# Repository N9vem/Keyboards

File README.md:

# Keyboards
My public keyboards, layouts or keyboard ideas, mostly work in progress.

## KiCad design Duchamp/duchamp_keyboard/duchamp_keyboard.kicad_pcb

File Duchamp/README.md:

Duchamp keyboard - The first pcb I ever finished

WARNING this pcb is untested yet

The board uses the larger pro micro which is mounted normally (the USB is facing downwards).

This PCB is may not be compatible with planck cases: the switch distance is 19.05 mm.

PCB size: 76 x 223.5 mm

BOM
- 1 large pro micro
- 47 Cherry MX style switch (clear body)
- 47 high speed diode, MiniMELF or through-hole
- 47 WS2812B LED
- 47 1206 capacitor ~100 nF
- 1 1206 resistor 300-500 Ω

Optional
- 1 EVQP0 switch for reset button

KNOWN ISSUES
- the switch distance are set for standard instead of 19 mm which can make them incompatible with planck switch plates.
- no mounting holes

The case for the keyboard is untested

<br />This work is licensed under a <a rel="license" href="http://creativecommons.org/licenses/by-sa/4.0/">Creative Commons Attribution-ShareAlike 4.0 International License</a>.

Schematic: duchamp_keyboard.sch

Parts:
C101, C102, C103, C104, C105, C106, C107, C108, C109, C110, C111, C112, C113, C114, C115, C116, C117, C118, C119, C120, C121, C122, C123, C124, C125, C126, C127, C128, C129, C130, C131, C132, C133, C134, C135, C136, C137, C138, C139, C140, C141, C142, C143, C144, C145, C146, C147: C_Small; C_1206_HandSoldering
D101, D102, D103, D104, D105, D106, D107, D108, D109, D110, D111, D112, D113, D114, D115, D116, D117, D118, D119, D120, D121, D122, D123, D124, D125, D126, D127, D128, D129, D130, D131, D132, D133, D134, D135, D136, D137, D138, D139, D140, D141, D142, D143, D144, D145, D146, D147: D; D_MiniMELF_Universal_Back
J_burn1: Conn_01x05; Pin_Header_Angled_1x05_Pitch2.00mm
J_ledstrip1: Conn_01x03; Pin_Header_Straight_1x03_Pitch2.00mm
LED101, LED102, LED103, LED104, LED105, LED106, LED107, LED108, LED109, LED110, LED111, LED112, LED113, LED114, LED115, LED116, LED117, LED118, LED119, LED120, LED121, LED122, LED123, LED124, LED125, LED126, LED127, LED128, LED129, LED130, LED131, LED132, LED133, LED134, LED135, LED136, LED137, LED138, LED139, LED140, LED141, LED142, LED143, LED144, LED145, LED146, LED147: WS2812B; CHERRY_MX_LED_WS2812b
R_DIN1: R; R_1206_HandSoldering
SW101: s1; CHERRY_PCB_100H
SW102: s2; CHERRY_PCB_100H
SW103: s3; CHERRY_PCB_100H
SW104: s4; CHERRY_PCB_100H
SW105: s5; CHERRY_PCB_100H
SW106: s6; CHERRY_PCB_100H
SW107: s7; CHERRY_PCB_100H
SW108: s8; CHERRY_PCB_100H
SW109: s9; CHERRY_PCB_100H
SW110: s10; CHERRY_PCB_100H
SW111: s11; CHERRY_PCB_100H
SW112: s12; CHERRY_PCB_100H
SW113: s13; CHERRY_PCB_100H
SW114: s14; CHERRY_PCB_100H
SW115: s15; CHERRY_PCB_100H
SW116: s16; CHERRY_PCB_100H
SW117: s17; CHERRY_PCB_100H
SW118: s18; CHERRY_PCB_100H
SW119: s19; CHERRY_PCB_100H
SW120: s20; CHERRY_PCB_100H
SW121: s21; CHERRY_PCB_100H
SW122: s22; CHERRY_PCB_100H
SW123: s23; CHERRY_PCB_100H
SW124: s24; CHERRY_PCB_100H
SW125: s25; CHERRY_PCB_100H
SW126: s26; CHERRY_PCB_100H
SW127: s27; CHERRY_PCB_100H
SW128: s28; CHERRY_PCB_100H
SW129: s29; CHERRY_PCB_100H
SW130: s30; CHERRY_PCB_100H
SW131: s31; CHERRY_PCB_100H
SW132: s32; CHERRY_PCB_100H
SW133: s33; CHERRY_PCB_100H
SW134: s34; CHERRY_PCB_100H
SW135: s35; CHERRY_PCB_100H
SW136: s36; CHERRY_PCB_100H
SW137: s37; CHERRY_PCB_100H
SW138: s38; CHERRY_PCB_100H
SW139: s39; CHERRY_PCB_100H
SW140: s40; CHERRY_PCB_100H
SW141: s41; CHERRY_PCB_100H
SW142: s42; CHERRY_PCB_200H
SW143: s43; CHERRY_PCB_100H
SW144: s44; CHERRY_PCB_100H
SW145: s45; CHERRY_PCB_100H
SW146: s46; CHERRY_PCB_100H
SW147: s47; CHERRY_PCB_100H
U101: ProMicro_large
res1: SW_Push; SW_SPST_EVQP0

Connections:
COL0: D101.1 (K), D113.1 (K), D125.1 (K), D137.1 (K), U101.1
COL1: D102.1 (K), D114.1 (K), D126.1 (K), D138.1 (K), U101.2
COL2: D103.1 (K), D115.1 (K), D127.1 (K), D139.1 (K), U101.10
COL3: D104.1 (K), D116.1 (K), D128.1 (K), D140.1 (K), U101.11
COL4: D105.1 (K), D117.1 (K), D129.1 (K), D141.1 (K), U101.13
COL5: D106.1 (K), D118.1 (K), D130.1 (K), D142.1 (K), U101.14
COL6: D107.1 (K), D119.1 (K), D131.1 (K), U101.15
COL7: D108.1 (K), D120.1 (K), D132.1 (K), D143.1 (K), U101.16
COL8: D109.1 (K), D121.1 (K), D133.1 (K), D144.1 (K), U101.17
COL9: D110.1 (K), D122.1 (K), D134.1 (K), D145.1 (K), U101.18
COL10: D111.1 (K), D123.1 (K), D135.1 (K), D146.1 (K), U101.19
COL11: D112.1 (K), D124.1 (K), D136.1 (K), D147.1 (K), U101.20
DIN: R_DIN1.1, U101.12
GND: C101.1, C102.1, C103.1, C104.1, C105.1, C106.1, C107.1, C108.1, C109.1, C110.1, C111.1, C112.1, C113.1, C114.1, C115.1, C116.1, C117.1, C118.1, C119.1, C120.1, C121.1, C122.1, C123.1, C124.1, C125.1, C126.1, C127.1, C128.1, C129.1, C130.1, C131.1, C132.1, C133.1, C134.1, C135.1, C136.1, C137.1, C138.1, C139.1, C140.1, C141.1, C142.1, C143.1, C144.1, C145.1, C146.1, C147.1, J_ledstrip1.1, LED101.3 (VSS), LED102.3 (VSS), LED103.3 (VSS), LED104.3 (VSS), LED105.3 (VSS), LED106.3 (VSS), LED107.3 (VSS), LED108.3 (VSS), LED109.3 (VSS), LED110.3 (VSS), LED111.3 (VSS), LED112.3 (VSS), LED113.3 (VSS), LED114.3 (VSS), LED115.3 (VSS), LED116.3 (VSS), LED117.3 (VSS), LED118.3 (VSS), LED119.3 (VSS), LED120.3 (VSS), LED121.3 (VSS), LED122.3 (VSS), LED123.3 (VSS), LED124.3 (VSS), LED125.3 (VSS), LED126.3 (VSS), LED127.3 (VSS), LED128.3 (VSS), LED129.3 (VSS), LED130.3 (VSS), LED131.3 (VSS), LED132.3 (VSS), LED133.3 (VSS), LED134.3 (VSS), LED136.3 (VSS), LED137.3 (VSS), LED138.3 (VSS), LED139.3 (VSS), LED140.3 (VSS), LED141.3 (VSS), LED142.3 (VSS), LED143.3 (VSS), LED144.3 (VSS), LED145.3 (VSS), LED146.3 (VSS), LED147.3 (VSS), U101.3, U101.4, U101.23, res1.2
unnamed: D101.2 (A), SW101.2
unnamed: D102.2 (A), SW102.2
unnamed: D103.2 (A), SW103.2
unnamed: D104.2 (A), SW104.2
unnamed: D105.2 (A), SW105.2
unnamed: D106.2 (A), SW106.2
unnamed: D107.2 (A), SW107.2
unnamed: D108.2 (A), SW108.2
unnamed: D109.2 (A), SW109.2
unnamed: D110.2 (A), SW110.2
unnamed: D111.2 (A), SW111.2
unnamed: D112.2 (A), SW112.2
unnamed: D113.2 (A), SW113.2
unnamed: D114.2 (A), SW114.2
unnamed: D115.2 (A), SW115.2
unnamed: D116.2 (A), SW116.2
unnamed: D117.2 (A), SW117.2
unnamed: D118.2 (A), SW118.2
unnamed: D119.2 (A), SW119.2
unnamed: D120.2 (A), SW120.2
unnamed: D121.2 (A), SW121.2
unnamed: D122.2 (A), SW122.2
unnamed: D123.2 (A), SW123.2
unnamed: D124.2 (A), SW124.2
unnamed: D125.2 (A), SW125.2
unnamed: D126.2 (A), SW126.2
unnamed: D127.2 (A), SW127.2
unnamed: D128.2 (A), SW128.2
unnamed: D129.2 (A), SW129.2
unnamed: D130.2 (A), SW130.2
unnamed: D131.2 (A), SW131.2
unnamed: D132.2 (A), SW132.2
unnamed: D133.2 (A), SW133.2
unnamed: D134.2 (A), SW134.2
unnamed: D135.2 (A), SW135.2
unnamed: D136.2 (A), SW136.2
unnamed: D137.2 (A), SW137.2
unnamed: D138.2 (A), SW138.2
unnamed: D139.2 (A), SW139.2
unnamed: D140.2 (A), SW140.2
unnamed: D141.2 (A), SW141.2
unnamed: D142.2 (A), SW142.2
unnamed: D143.2 (A), SW143.2
unnamed: D144.2 (A), SW144.2
unnamed: D145.2 (A), SW145.2
unnamed: D146.2 (A), SW146.2
unnamed: D147.2 (A), SW147.2
unnamed: J_ledstrip1.2, LED147.2 (DOUT)
unnamed: LED101.2 (DOUT), LED102.4 (DIN)
unnamed: LED101.4 (DIN), R_DIN1.2
unnamed: LED102.2 (DOUT), LED103.4 (DIN)
unnamed: LED103.2 (DOUT), LED104.4 (DIN)
unnamed: LED104.2 (DOUT), LED105.4 (DIN)
unnamed: LED105.2 (DOUT), LED106.4 (DIN)
unnamed: LED106.2 (DOUT), LED107.4 (DIN)
unnamed: LED107.2 (DOUT), LED108.4 (DIN)
unnamed: LED108.2 (DOUT), LED109.4 (DIN)
unnamed: LED109.2 (DOUT), LED110.4 (DIN)
unnamed: LED110.2 (DOUT), LED111.4 (DIN)
unnamed: LED111.2 (DOUT), LED112.4 (DIN)
unnamed: LED112.2 (DOUT), LED113.4 (DIN)
unnamed: LED113.2 (DOUT), LED114.4 (DIN)
unnamed: LED114.2 (DOUT), LED115.4 (DIN)
unnamed: LED115.2 (DOUT), LED116.4 (DIN)
unnamed: LED116.2 (DOUT), LED117.4 (DIN)
unnamed: LED117.2 (DOUT), LED118.4 (DIN)
unnamed: LED118.2 (DOUT), LED119.4 (DIN)
unnamed: LED119.2 (DOUT), LED120.4 (DIN)
unnamed: LED120.2 (DOUT), LED121.4 (DIN)
unnamed: LED121.2 (DOUT), LED122.4 (DIN)
unnamed: LED122.2 (DOUT), LED123.4 (DIN)
unnamed: LED123.2 (DOUT), LED124.4 (DIN)
unnamed: LED124.2 (DOUT), LED125.4 (DIN)
unnamed: LED125.2 (DOUT), LED126.4 (DIN)
unnamed: LED126.2 (DOUT), LED127.4 (DIN)
unnamed: LED127.2 (DOUT), LED128.4 (DIN)
unnamed: LED128.2 (DOUT), LED129.4 (DIN)
unnamed: LED129.2 (DOUT), LED130.4 (DIN)
unnamed: LED130.2 (DOUT), LED131.4 (DIN)
unnamed: LED131.2 (DOUT), LED132.4 (DIN)
unnamed: LED132.2 (DOUT), LED133.4 (DIN)
unnamed: LED133.2 (DOUT), LED134.4 (DIN)
unnamed: LED134.2 (DOUT), LED135.4 (DIN)
unnamed: LED135.2 (DOUT), LED136.4 (DIN)
unnamed: LED136.2 (DOUT), LED137.4 (DIN)
unnamed: LED137.2 (DOUT), LED138.4 (DIN)
unnamed: LED138.2 (DOUT), LED139.4 (DIN)
unnamed: LED139.2 (DOUT), LED140.4 (DIN)
unnamed: LED140.2 (DOUT), LED141.4 (DIN)
unnamed: LED141.2 (DOUT), LED142.4 (DIN)
unnamed: LED142.2 (DOUT), LED143.4 (DIN)
unnamed: LED143.2 (DOUT), LED144.4 (DIN)
unnamed: LED144.2 (DOUT), LED145.4 (DIN)
unnamed: LED145.2 (DOUT), LED146.4 (DIN)
unnamed: LED146.2 (DOUT), LED147.4 (DIN)
ROW0: SW101.1, SW102.1, SW103.1, SW104.1, SW105.1, SW106.1, SW107.1, SW108.1, SW109.1, SW110.1, SW111.1, SW112.1, U101.6
ROW1: SW113.1, SW114.1, SW115.1, SW116.1, SW117.1, SW118.1, SW119.1, SW120.1, SW121.1, SW122.1, SW123.1, SW124.1, U101.7
ROW2: SW125.1, SW126.1, SW127.1, SW128.1, SW129.1, SW130.1, SW131.1, SW132.1, SW133.1, SW134.1, SW135.1, SW136.1, U101.8
ROW3: SW137.1, SW138.1, SW139.1, SW140.1, SW141.1, SW142.1, SW143.1, SW144.1, SW145.1, SW146.1, SW147.1, U101.9
RST: U101.22, res1.1
VCC: C101.2, C102.2, C103.2, C104.2, C105.2, C106.2, C107.2, C108.2, C109.2, C110.2, C111.2, C112.2, C113.2, C114.2, C115.2, C116.2, C117.2, C118.2, C119.2, C120.2, C121.2, C122.2, C123.2, C124.2, C125.2, C126.2, C127.2, C128.2, C129.2, C130.2, C131.2, C132.2, C133.2, C134.2, C135.2, C136.2, C137.2, C138.2, C139.2, C140.2, C141.2, C142.2, C143.2, C144.2, C145.2, C146.2, C147.2, J_ledstrip1.3, LED101.1 (VDD), LED102.1 (VDD), LED103.1 (VDD), LED104.1 (VDD), LED105.1 (VDD), LED106.1 (VDD), LED107.1 (VDD), LED108.1 (VDD), LED109.1 (VDD), LED110.1 (VDD), LED111.1 (VDD), LED112.1 (VDD), LED113.1 (VDD), LED114.1 (VDD), LED115.1 (VDD), LED116.1 (VDD), LED117.1 (VDD), LED118.1 (VDD), LED119.1 (VDD), LED120.1 (VDD), LED121.1 (VDD), LED122.1 (VDD), LED123.1 (VDD), LED124.1 (VDD), LED125.1 (VDD), LED126.1 (VDD), LED127.1 (VDD), LED128.1 (VDD), LED129.1 (VDD), LED130.1 (VDD), LED131.1 (VDD), LED132.1 (VDD), LED133.1 (VDD), LED134.1 (VDD), LED135.1 (VDD), LED136.1 (VDD), LED137.1 (VDD), LED138.1 (VDD), LED139.1 (VDD), LED140.1 (VDD), LED141.1 (VDD), LED142.1 (VDD), LED143.1 (VDD), LED144.1 (VDD), LED145.1 (VDD), LED146.1 (VDD), LED147.1 (VDD), U101.21

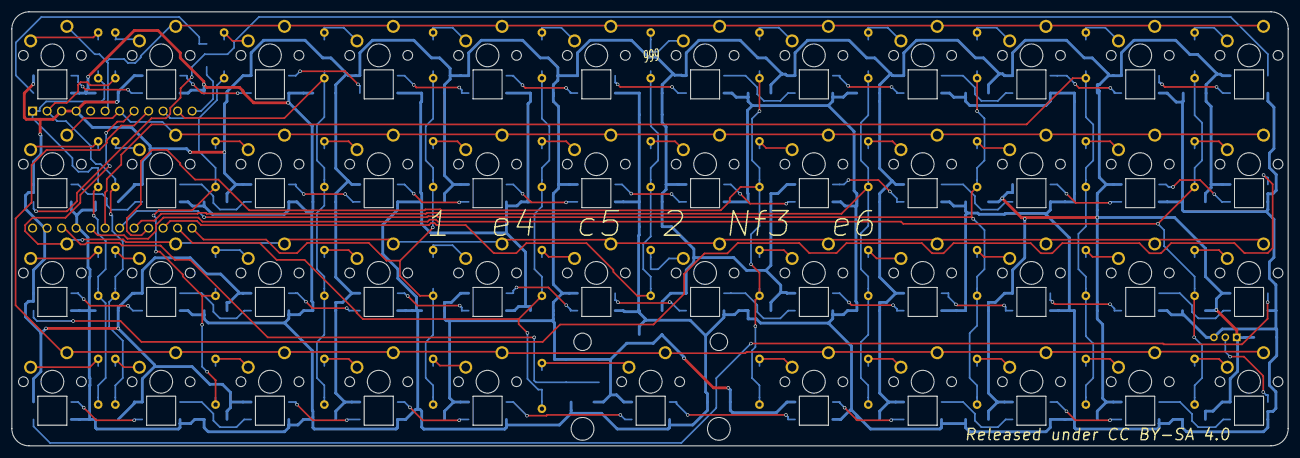
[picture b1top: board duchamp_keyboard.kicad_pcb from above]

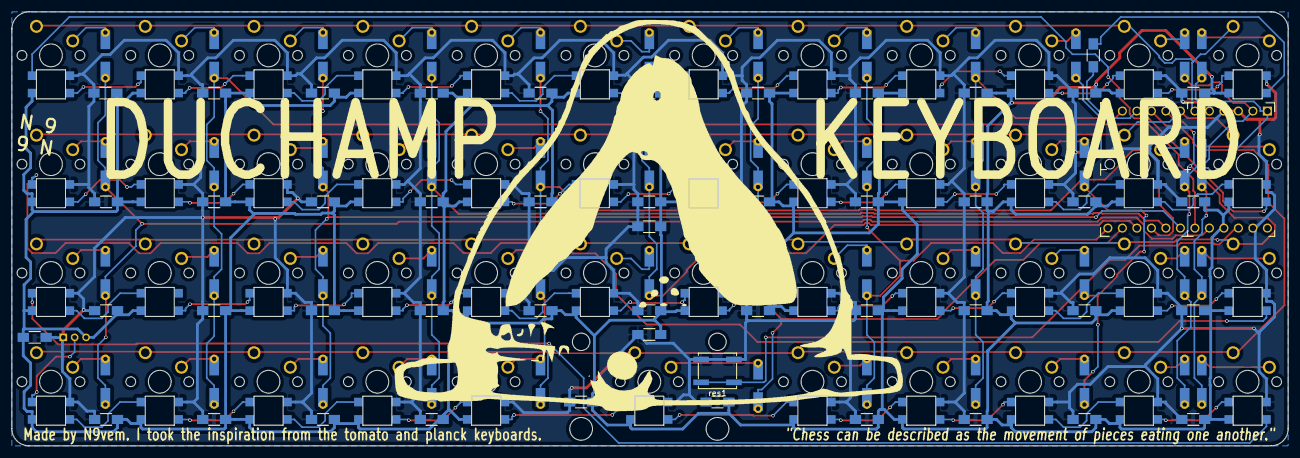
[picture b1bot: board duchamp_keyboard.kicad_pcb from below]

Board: 2 copper layers, 223.5 x 76.0 mm, 192 parts (97 on the bottom side), 115 nets.

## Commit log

2018-07-31 changed folders
2023-03-24 The update I should have done a long time ago
    These files are 5 years old, even I don't know what is inside them 🤗
2023-03-26 Case design for v0.1

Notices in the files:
Duchamp/duchamp_keyboard/duchamp_keyboard.kicad_pcb:
Released under CC BY-SA 4.0
